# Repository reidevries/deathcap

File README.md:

# deathcap wavefolder
I did end up testing this and the CMOS part worked but was quiet and the envelope follower didn't seem to have the right gain. I don't remember if the VCA part worked at all, but I do remember that something was wrong with that too.

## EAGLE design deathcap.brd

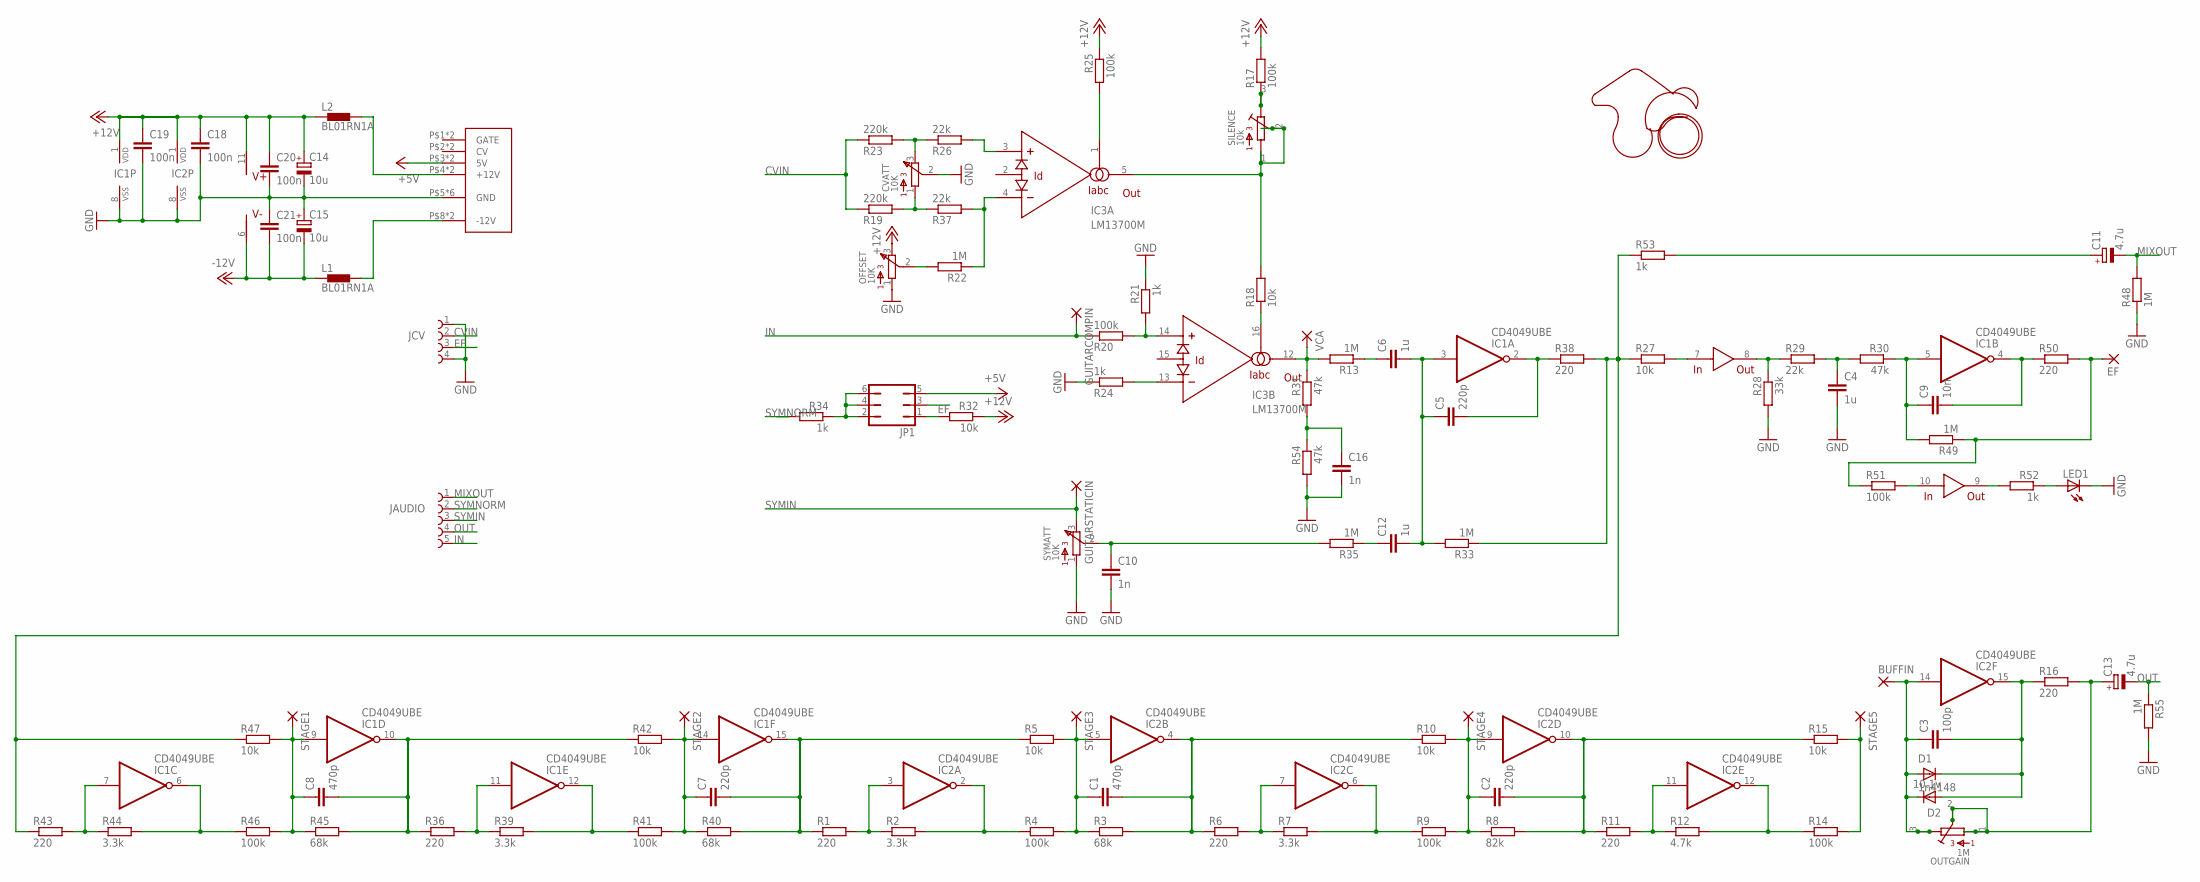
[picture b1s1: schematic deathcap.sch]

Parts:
BUFFIN: 2,0/0,9-S
C1, C8: 470p; C1206
C2, C5, C7: 220p; C1206
C3: 100p; C1206
C4, C6, C12: 1u; C1206
C9: 10n; C1206
C10, C16: 1n; C1206
C11, C13: 4.7u; PANASONIC_D
C14, C15: 10u; PANASONIC_D
C18, C19, C20, C21: 100n; C1206
CVATT: 10K; 91
D1: 1n4148; SOD-123_MINI-SMA
D2: 10.1v; SOD-123_MINI-SMA
EF: 2,0/0,9-S
GUITARCOMPIN: 2,0/0,9-S
GUITARSTATICIN: 2,0/0,9-S
IC1, IC2: CD4049UBE; DIL16
IC3: LM13700M; SO16
JAUDIO: 61300511121
JCV: 61300411121
JP1: JP3Q
L1, L2: BL01RN1A
LED1: LED5MM
OFFSET: 10K; 91
OUTGAIN: 1M; 3386-MULTI
R1, R6, R11, R16, R36, R38, R43, R50: 220; R1206
R2, R7, R39, R44: 3.3k; R1206
R3, R40, R45: 68k; R1206
R4, R9, R14, R17, R20, R25, R41, R46, R51: 100k; R1206
R5, R10, R15, R18, R27, R32, R42, R47: 10k; R1206
R8: 82k; R1206
R12: 4.7k; R1206
R13, R22, R33, R35, R48, R49, R55: 1M; R1206
R19, R23: 220k; R1206
R21, R24, R34, R52, R53: 1k; R1206
R26, R29, R37: 22k; R1206
R28: 33k; R1206
R30, R31, R54: 47k; R1206
SILENCE: 10k; 3386-MULTI
STAGE1, STAGE2, STAGE3, STAGE4, STAGE5: 2,0/0,9-S
SYMATT: 10K; 91
U$1: EUROPWR
U$2: LOGO
VCA: 2,0/0,9-S

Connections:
+5V: JP1.5, U$1.P$3 (5V), U$1.P$14 (5V)
+12V: C14.+, C18.1, C19.1, C20.1, IC1.1 (VDD), IC2.1 (VDD), IC3.11 (V+), L2.1, OFFSET.3, R17.2, R25.1, R32.1
-12V: C15.-, C21.2, IC3.6 (V-), L1.1
CVIN: JCV.2, R19.1, R23.1
EF: JCV.3, JP1.3
GND: C4.2, C10.2, C14.-, C15.+, C16.2, C18.2, C19.2, C20.2, C21.1, CVATT.2, IC1.8 (VSS), IC2.8 (VSS), JCV.1, JCV.4, LED1.K (C), OFFSET.1, R21.1, R24.1, R28.2, R48.1, R54.2, R55.2, SYMATT.1, U$1.P$5 (GND), U$1.P$6 (GND), U$1.P$7 (GND), U$1.P$10 (GND), U$1.P$11 (GND), U$1.P$12 (GND)
IN: GUITARCOMPIN.1, JAUDIO.5, R20.1
MIXOUT: C11.-, JAUDIO.1, R48.2
unnamed: IC3.16 (IABC), R18.1
unnamed: C1.1, IC2.5 (I), R3.1, R4.2, R5.2, STAGE3.1
unnamed: C1.2, IC2.4 (O), R3.2, R6.1, R10.1
unnamed: IC2.3 (I), R1.2, R2.1
unnamed: IC2.2 (O), R2.2, R4.1
unnamed: C3.2, D1.C, D2.A, IC2.15 (O), R16.1
unnamed: C2.1, IC2.9 (I), R8.1, R9.2, R10.2, STAGE4.1
unnamed: C2.2, IC2.10 (O), R8.2, R11.1, R15.1
unnamed: IC2.7 (I), R6.2, R7.1
unnamed: IC2.6 (O), R7.2, R9.1
unnamed: EF.1, R49.1, R50.2, R51.1
unnamed: BUFFIN.1, C3.1, D1.A, D2.C, IC2.14 (I), OUTGAIN.3, OUTGAIN.6
unnamed: C9.2, IC1.4 (O), R50.1
unnamed: IC2.11 (I), R11.2, R12.1
unnamed: IC2.12 (O), R12.2, R14.1
unnamed: R1.1, R5.1
unnamed: CVATT.1, R19.2, R37.1
unnamed: IC3.13 (-IN), R24.2
unnamed: CVATT.3, R23.2, R26.1
unnamed: IC3.14 (+IN), R20.2, R21.2
unnamed: IC3.5 (OUT), R18.2, SILENCE.1, SILENCE.2, SILENCE.4, SILENCE.5
unnamed: C6.1, R13.1
unnamed: IC3.3 (+IN), R26.2
unnamed: C12.1, R35.1
unnamed: OFFSET.2, R22.2
unnamed: IC3.1 (IABC), R25.2
unnamed: IC3.7 (IN), R27.2
unnamed: IC3.8 (OUT), R28.1, R29.1
unnamed: C4.1, R29.2, R30.2
unnamed: R17.1, SILENCE.3, SILENCE.6
unnamed: C5.1, C6.2, C12.2, IC1.3 (I), R33.2
unnamed: C5.2, IC1.2 (O), R38.1
unnamed: IC3.10 (IN), R51.2
unnamed: IC3.9 (OUT), R52.2
unnamed: JP1.2, JP1.4, JP1.6, R34.1
unnamed: IC3.12 (OUT), R13.2, R31.1, VCA.1
unnamed: JP1.1, R32.2
unnamed: IC3.4 (-IN), R22.1, R37.2
unnamed: C10.1, R35.2, SYMATT.2
unnamed: R27.1, R33.1, R38.2, R43.1, R47.1, R53.1
unnamed: C7.1, IC1.14 (I), R40.1, R41.2, R42.2, STAGE2.1
unnamed: C7.2, IC1.15 (O), R40.2
unnamed: IC1.11 (I), R36.2, R39.1
unnamed: IC1.12 (O), R39.2, R41.1
unnamed: R36.1, R42.1
unnamed: C8.1, IC1.9 (I), R45.1, R46.2, R47.2, STAGE1.1
unnamed: C8.2, IC1.10 (O), R45.2
unnamed: IC1.7 (I), R43.2, R44.1
unnamed: IC1.6 (O), R44.2, R46.1
unnamed: C9.1, IC1.5 (I), R30.1, R49.2
unnamed: LED1.A, R52.1
unnamed: C11.+, R53.2
unnamed: L2.2, U$1.P$4 (+12V), U$1.P$13 (+12V)
unnamed: L1.2, U$1.P$8 (-12V), U$1.P$9 (-12V)
unnamed: C16.1, R31.2, R54.1
unnamed: C13.+, OUTGAIN.1, OUTGAIN.2, OUTGAIN.4, OUTGAIN.5, R16.2
unnamed: R14.2, R15.2, STAGE5.1
OUT: C13.-, JAUDIO.4, R55.1
SYMIN: GUITARSTATICIN.1, JAUDIO.3, SYMATT.3
SYMNORM: JAUDIO.2, R34.2

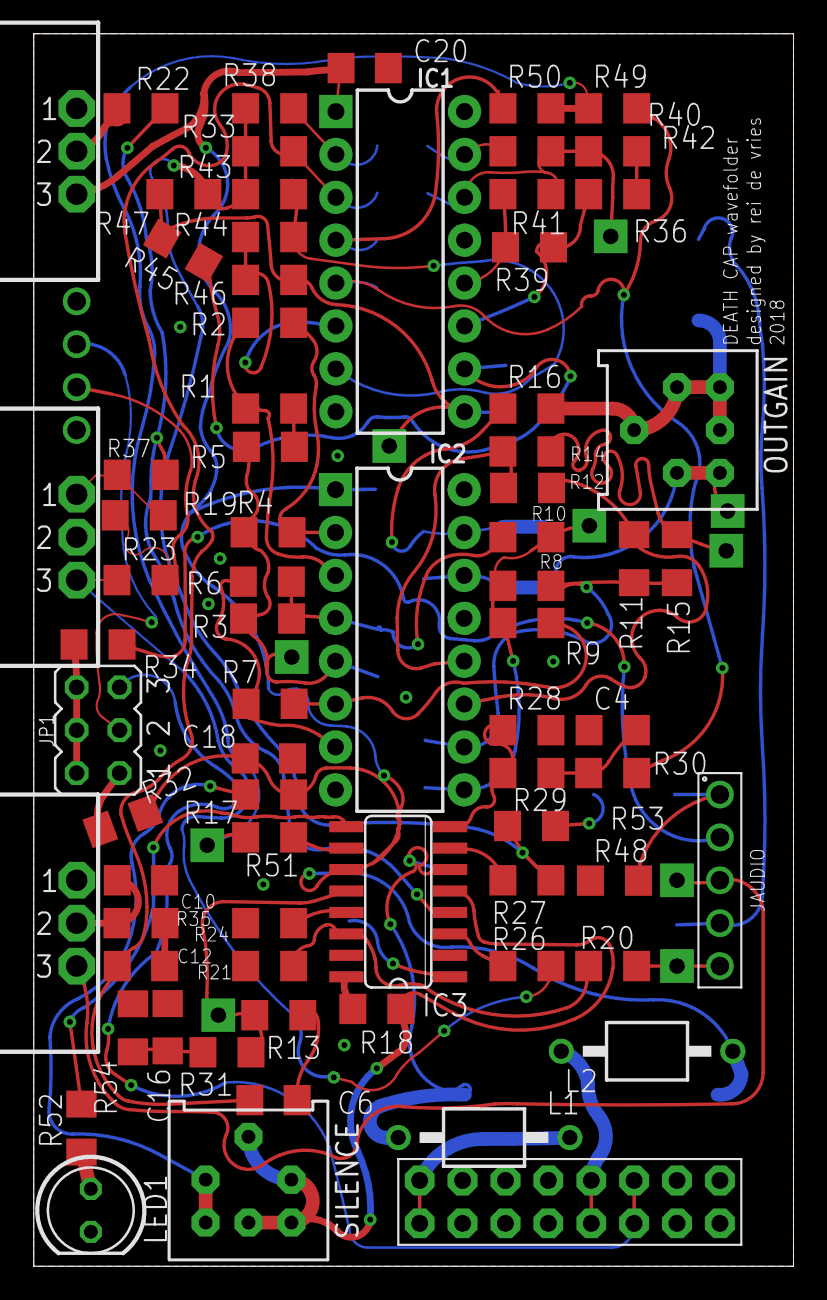
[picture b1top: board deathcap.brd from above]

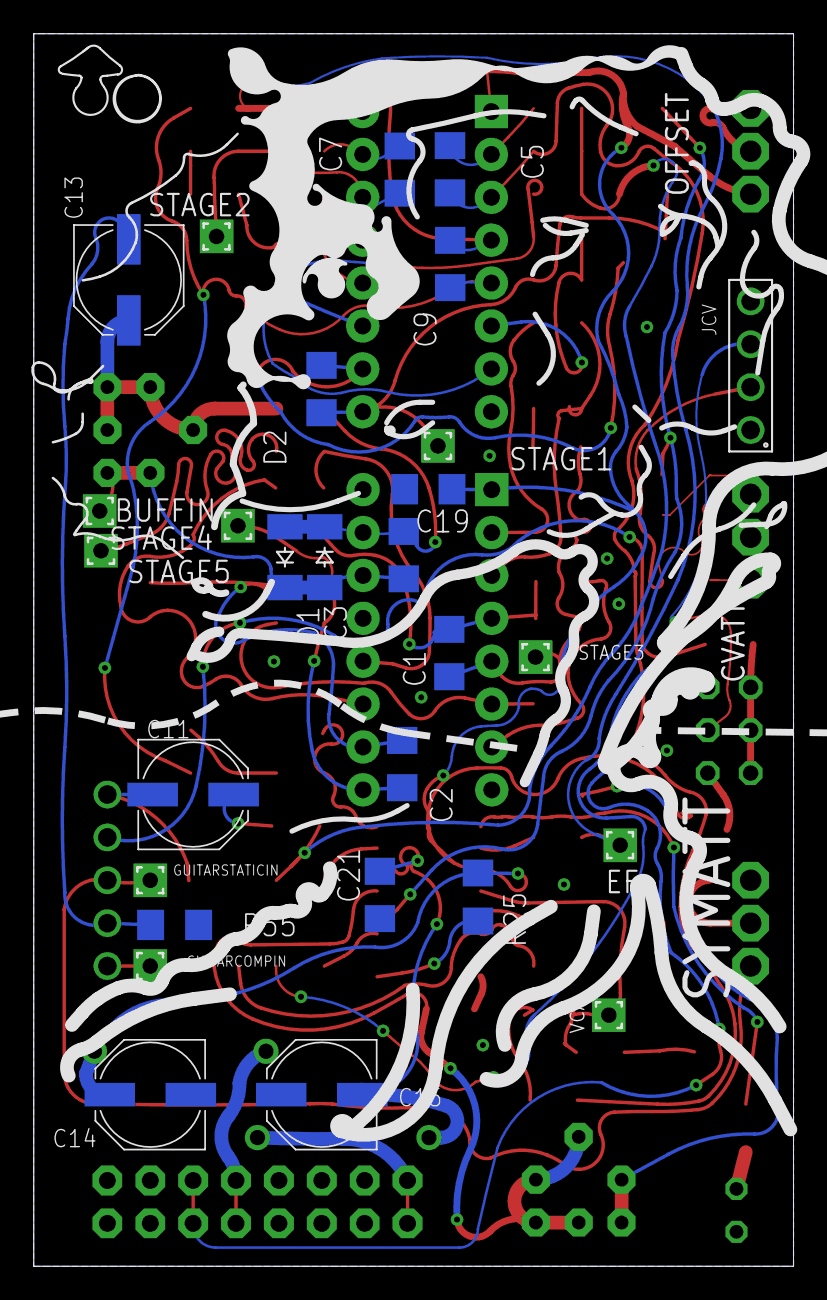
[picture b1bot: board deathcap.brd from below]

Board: 2 copper layers, 45.0 x 73.0 mm, 103 parts (29 on the bottom side), 68 nets.

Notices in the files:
parts and their libraries:
Board-to-Board: Copyright: Würth Elektronik
